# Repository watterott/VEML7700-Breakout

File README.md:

# VEML7700-Breakout
Breakout with Vishay VEML7700 Light Sensor.

* Open-Source and released under the [Creative Commons Attribution Share-Alike License](https://creativecommons.org/licenses/by-sa/4.0/).
* **[Documentation on learn.watterott.com](https://learn.watterott.com)**

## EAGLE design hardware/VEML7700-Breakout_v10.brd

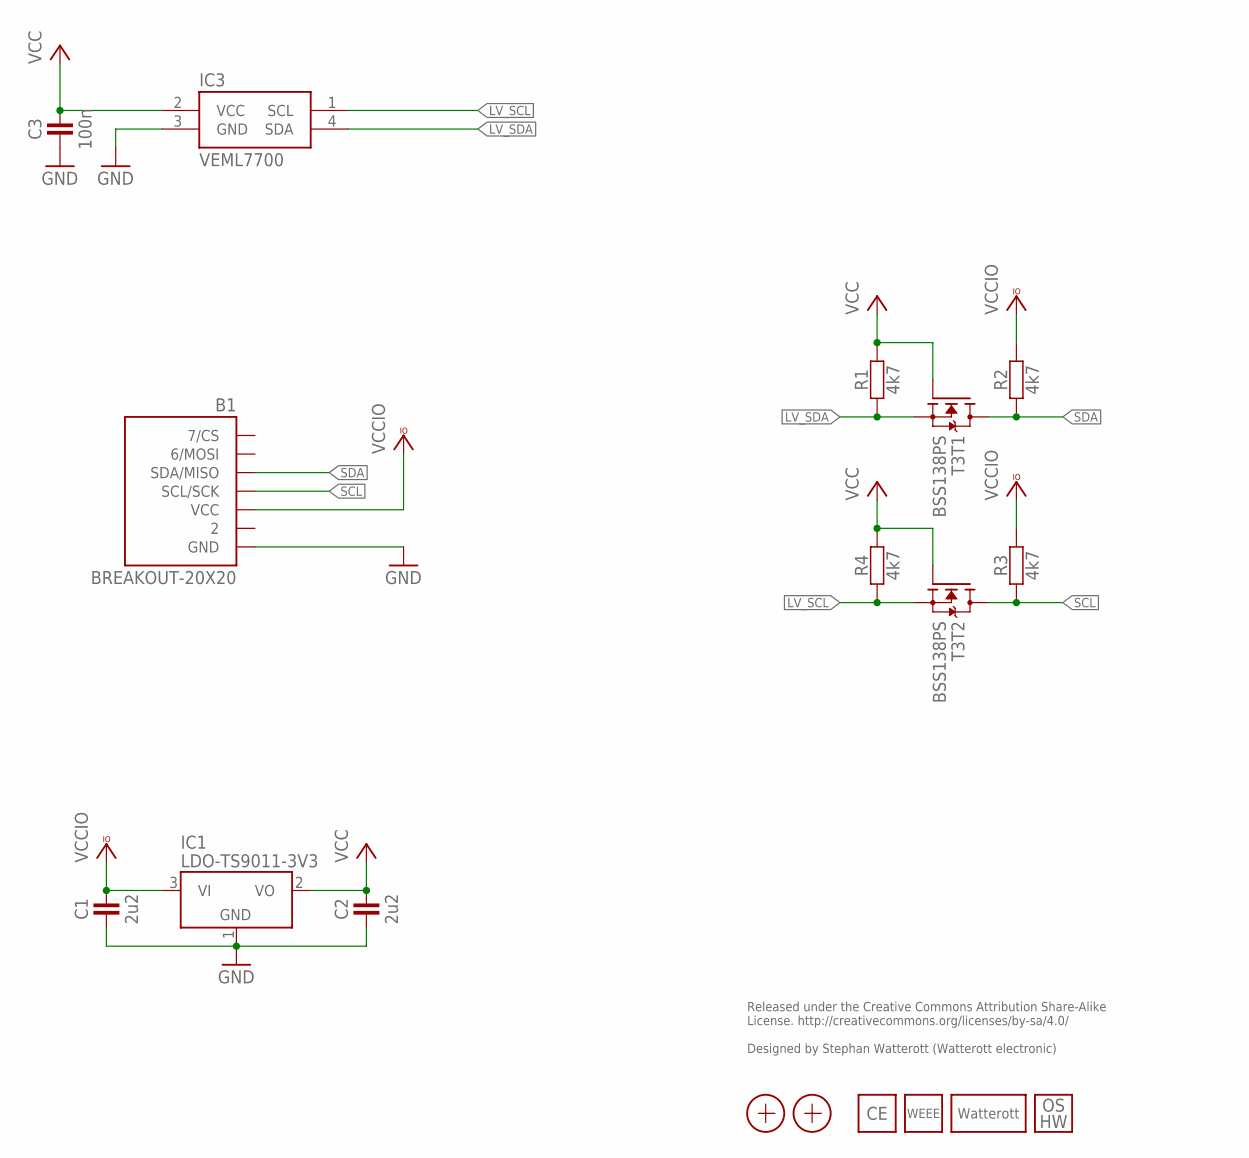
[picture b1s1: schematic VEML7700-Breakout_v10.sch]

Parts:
B1: BREAKOUT-20X20
C1, C2: 2u2; C0402
C3: 100n; C0402
IC1: LDO-TS9011-3V3; SOT23
IC3: VEML7700
LOGO3: LOGO_WEEE-4; WEEE_4MM
LOGO4: LOGO_CE-4; CE_4MM
LOGO5: LOGO_SPARK-4; SPARK_4MM
LOGO6: LOGO_OSHW-2; OSHW_2MM
R1, R2, R3, R4: 4k7; C0402
T3: BSS138PS; SOT363
X1, X2: PASSER-07; PASSER_07MM

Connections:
GND: B1.GND, C1.1, C2.1, C3.1, IC1.1 (GND), IC3.3 (GND)
LV_SCL: IC3.1 (SCL), R4.1, T3.4 (S)
LV_SDA: IC3.4 (SDA), R1.1, T3.1 (S)
SCL: B1.SCL/SCK, R3.1, T3.3 (D)
SDA: B1.SDA/MISO, R2.1, T3.6 (D)
VCC: C2.2, C3.2, IC1.2 (VO), IC3.2 (VCC), R1.2, R4.2, T3.2 (G), T3.5 (G)
VCCIO: B1.VCC, C1.2, IC1.3 (VI), R2.2, R3.2

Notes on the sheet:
Released under the Creative Commons Attribution Share-Alike License. http://creativecommons.org/licenses/by-sa/4.0/ Designed by Stephan Watterott (Watterott electronic)

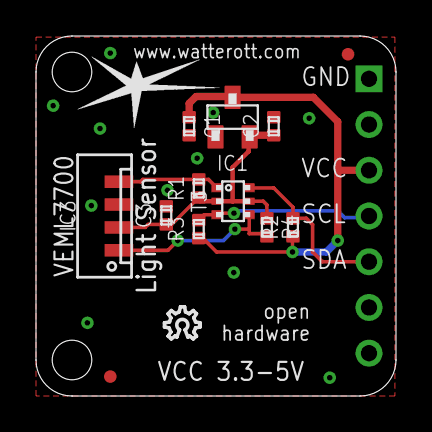
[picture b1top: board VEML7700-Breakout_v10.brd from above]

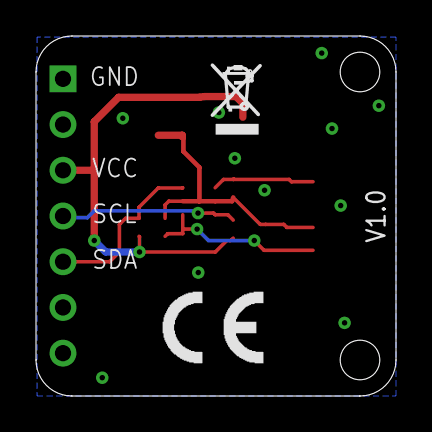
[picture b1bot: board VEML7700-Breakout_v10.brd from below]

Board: 2 copper layers, 20.0 x 20.0 mm, 17 parts (2 on the bottom side), 7 nets.

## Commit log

2019-02-02 added readme
2019-11-03 added schematics and layout
